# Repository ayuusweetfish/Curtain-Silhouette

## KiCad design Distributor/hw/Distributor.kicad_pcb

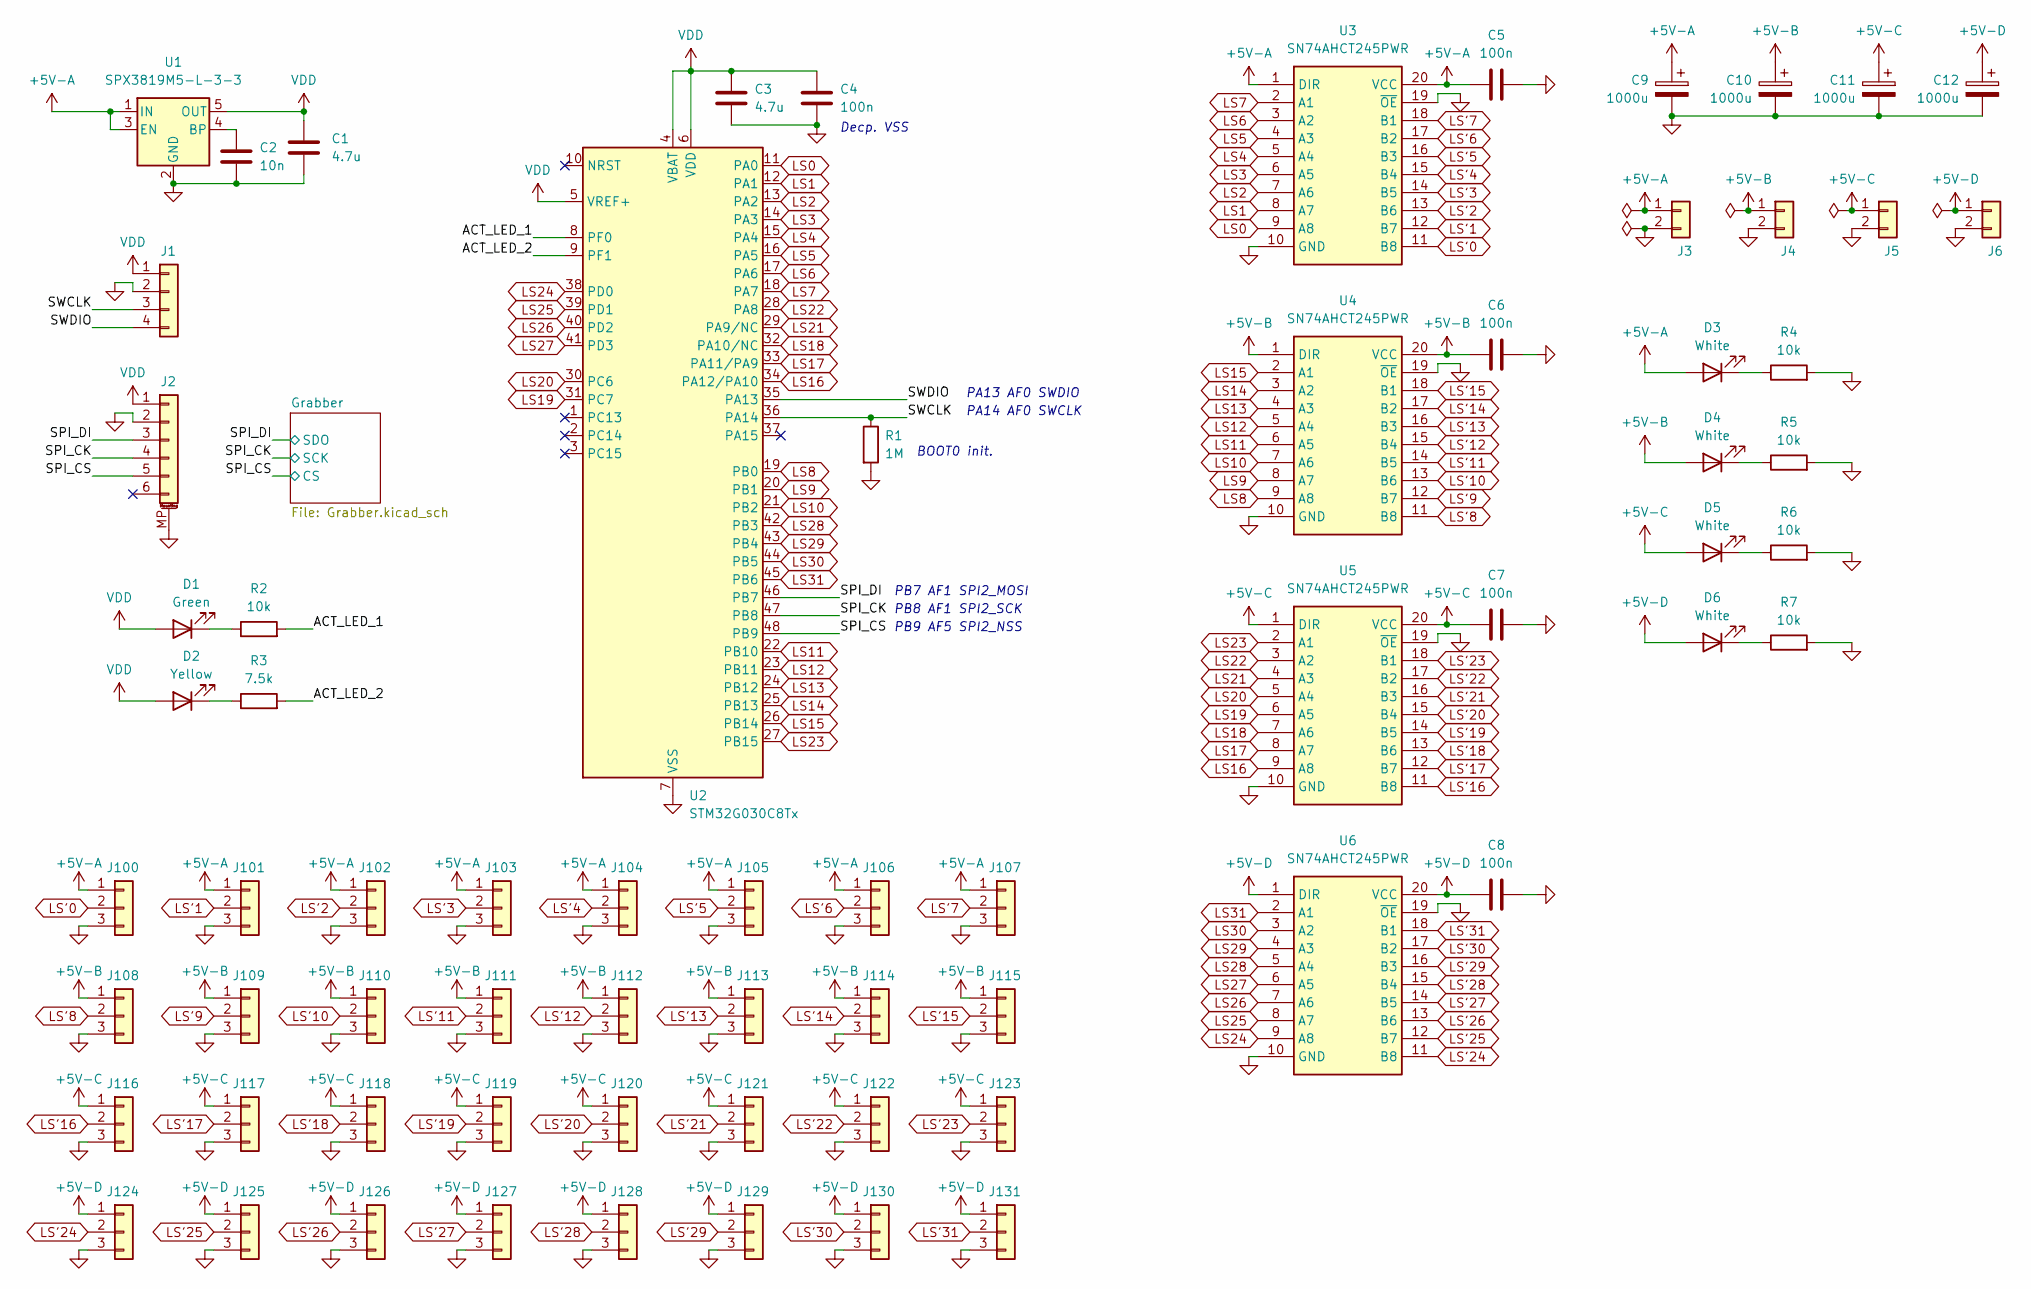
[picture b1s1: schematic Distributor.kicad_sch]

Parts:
C1, C3: 4.7u; C_0603_1608Metric
C2: 10n; C_0603_1608Metric
C4, C5, C6, C7, C8: 100n; C_0603_1608Metric
C9, C10, C11, C12: 1000u; CP_Elec_8x10.5
D1: Green; LED_0603_1608Metric
D2: Yellow; LED_0603_1608Metric
D3, D4, D5, D6: White; LED_0603_1608Metric
J1: Conn_01x04; TestPoints_1x04_P2.0
J2: Conn_01x06_MountingPin; Jushuo_AFC07-S06FCA-00_1x6-1MP_P0.50_Horizontal
J3, J4, J5, J6: Conn_01x02; PinHeader_1x02_P2.54mm_Vertical
J100, J101, J102, J103, J104, J105, J106, J107, J108, J109, J110, J111, J112, J113, J114, J115, J116, J117, J118, J119, J120, J121, J122, J123, J124, J125, J126, J127, J128, J129, J130, J131: Conn_01x03; PinHeader_1x03_P2.54mm_Vertical
R1: 1M; R_0603_1608Metric
R2, R4, R5, R6, R7: 10k; R_0603_1608Metric
R3: 7.5k; R_0603_1608Metric
U1: SPX3819M5-L-3-3; SOT-23-5
U2: STM32G030C8Tx; LQFP-48_7x7mm_P0.5mm
U3, U4, U5, U6: SN74AHCT245PWR; SOP65P640X120-20N; Manufacturer_Part_Number SN74AHCT245PWR; Mouser Part Number 595-SN74AHCT245PWR

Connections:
+5V-A: C5.1, C9.1, D3.2 (A), J3.1, J100.1, J101.1, J102.1, J103.1, J104.1, J105.1, J106.1, J107.1, U1.1 (IN), U1.3 (EN), U3.1 (DIR), U3.20 (VCC)
+5V-B: C6.1, C10.1, D4.2 (A), J4.1, J108.1, J109.1, J110.1, J111.1, J112.1, J113.1, J114.1, J115.1, U4.1 (DIR), U4.20 (VCC)
+5V-C: C7.1, C11.1, D5.2 (A), J5.1, J116.1, J117.1, J118.1, J119.1, J120.1, J121.1, J122.1, J123.1, U5.1 (DIR), U5.20 (VCC)
+5V-D: C8.1, C12.1, D6.2 (A), J6.1, J124.1, J125.1, J126.1, J127.1, J128.1, J129.1, J130.1, J131.1, U6.1 (DIR), U6.20 (VCC)
/ACT_LED_1: R2.2, U2.8 (PF0)
/ACT_LED_2: R3.2, U2.9 (PF1)
/SPI_CK: J2.4, U2.47 (PB8); also elsewhere on the board
/SPI_CS: J2.5, U2.48 (PB9); also elsewhere on the board
/SPI_DI: J2.3, U2.46 (PB7); also elsewhere on the board
/SWCLK: J1.3, R1.1, U2.36 (PA14)
/SWDIO: J1.4, U2.35 (PA13)
GND: C1.2, C2.2, C3.2, C4.2, C5.2, C6.2, C7.2, C8.2, C9.2, C10.2, C11.2, C12.2, J1.2, J2.2, J2.MP (MountPin), J3.2, J4.2, J5.2, J6.2, J100.3, J101.3, J102.3, J103.3, J104.3, J105.3, J106.3, J107.3, J108.3, J109.3, J110.3, J111.3, J112.3, J113.3, J114.3, J115.3, J116.3, J117.3, J118.3, J119.3, J120.3, J121.3, J122.3, J123.3, J124.3, J125.3, J126.3, J127.3, J128.3, J129.3, J130.3, J131.3, R1.2, R4.2, R5.2, R6.2, R7.2, U1.2 (GND), U2.7 (VSS), U3.10 (GND), U3.19 (~OE), U4.10 (GND), U4.19 (~OE), U5.10 (GND), U5.19 (~OE), U6.10 (GND), U6.19 (~OE); also elsewhere on the board
LS0: U2.11 (PA0), U3.9 (A8)
LS1: U2.12 (PA1), U3.8 (A7)
LS2: U2.13 (PA2), U3.7 (A6)
LS3: U2.14 (PA3), U3.6 (A5)
LS4: U2.15 (PA4), U3.5 (A4)
LS5: U2.16 (PA5), U3.4 (A3)
LS6: U2.17 (PA6), U3.3 (A2)
LS7: U2.18 (PA7), U3.2 (A1)
LS8: U2.19 (PB0), U4.9 (A8)
LS9: U2.20 (PB1), U4.8 (A7)
LS10: U2.21 (PB2), U4.7 (A6)
LS11: U2.22 (PB10), U4.6 (A5)
LS12: U2.23 (PB11), U4.5 (A4)
LS13: U2.24 (PB12), U4.4 (A3)
LS14: U2.25 (PB13), U4.3 (A2)
LS15: U2.26 (PB14), U4.2 (A1)
LS16: U2.34 (PA12/PA10), U5.9 (A8)
LS17: U2.33 (PA11/PA9), U5.8 (A7)
LS18: U2.32 (PA10/NC), U5.7 (A6)
LS19: U2.31 (PC7), U5.6 (A5)
LS20: U2.30 (PC6), U5.5 (A4)
LS21: U2.29 (PA9/NC), U5.4 (A3)
LS22: U2.28 (PA8), U5.3 (A2)
LS23: U2.27 (PB15), U5.2 (A1)
LS24: U2.38 (PD0), U6.9 (A8)
LS25: U2.39 (PD1), U6.8 (A7)
LS26: U2.40 (PD2), U6.7 (A6)
LS27: U2.41 (PD3), U6.6 (A5)
LS28: U2.42 (PB3), U6.5 (A4)
LS29: U2.43 (PB4), U6.4 (A3)
LS30: U2.44 (PB5), U6.3 (A2)
LS31: U2.45 (PB6), U6.2 (A1)
LS'0: J100.2, U3.11 (B8)
LS'1: J101.2, U3.12 (B7)
LS'2: J102.2, U3.13 (B6)
LS'3: J103.2, U3.14 (B5)
LS'4: J104.2, U3.15 (B4)
LS'5: J105.2, U3.16 (B3)
LS'6: J106.2, U3.17 (B2)
LS'7: J107.2, U3.18 (B1)
LS'8: J108.2, U4.11 (B8)
LS'9: J109.2, U4.12 (B7)
LS'10: J110.2, U4.13 (B6)
LS'11: J111.2, U4.14 (B5)
LS'12: J112.2, U4.15 (B4)
LS'13: J113.2, U4.16 (B3)
LS'14: J114.2, U4.17 (B2)
LS'15: J115.2, U4.18 (B1)
LS'16: J116.2, U5.11 (B8)
LS'17: J117.2, U5.12 (B7)
LS'18: J118.2, U5.13 (B6)
LS'19: J119.2, U5.14 (B5)
LS'20: J120.2, U5.15 (B4)
LS'21: J121.2, U5.16 (B3)
LS'22: J122.2, U5.17 (B2)
LS'23: J123.2, U5.18 (B1)
LS'24: J124.2, U6.11 (B8)
LS'25: J125.2, U6.12 (B7)
LS'26: J126.2, U6.13 (B6)
LS'27: J127.2, U6.14 (B5)
LS'28: J128.2, U6.15 (B4)
LS'29: J129.2, U6.16 (B3)
LS'30: J130.2, U6.17 (B2)
LS'31: J131.2, U6.18 (B1)
unnamed: D1.1 (K), R2.1
unnamed: D2.1 (K), R3.1
unnamed: D3.1 (K), R4.1
unnamed: D4.1 (K), R5.1
unnamed: D5.1 (K), R6.1
unnamed: D6.1 (K), R7.1
unnamed: C2.1, U1.4 (BP)
VDD: C1.1, C3.1, C4.1, D1.2 (A), D2.2 (A), J1.1, J2.1, U1.5 (OUT), U2.4 (VBAT), U2.5 (VREF+), U2.6 (VDD); also elsewhere on the board

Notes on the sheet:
PA14 AF0 SWCLK
PB8 AF1 SPI2_SCK
PB7 AF1 SPI2_MOSI
BOOT0 init.
Decp. VSS
PB9 AF5 SPI2_NSS
PA13 AF0 SWDIO

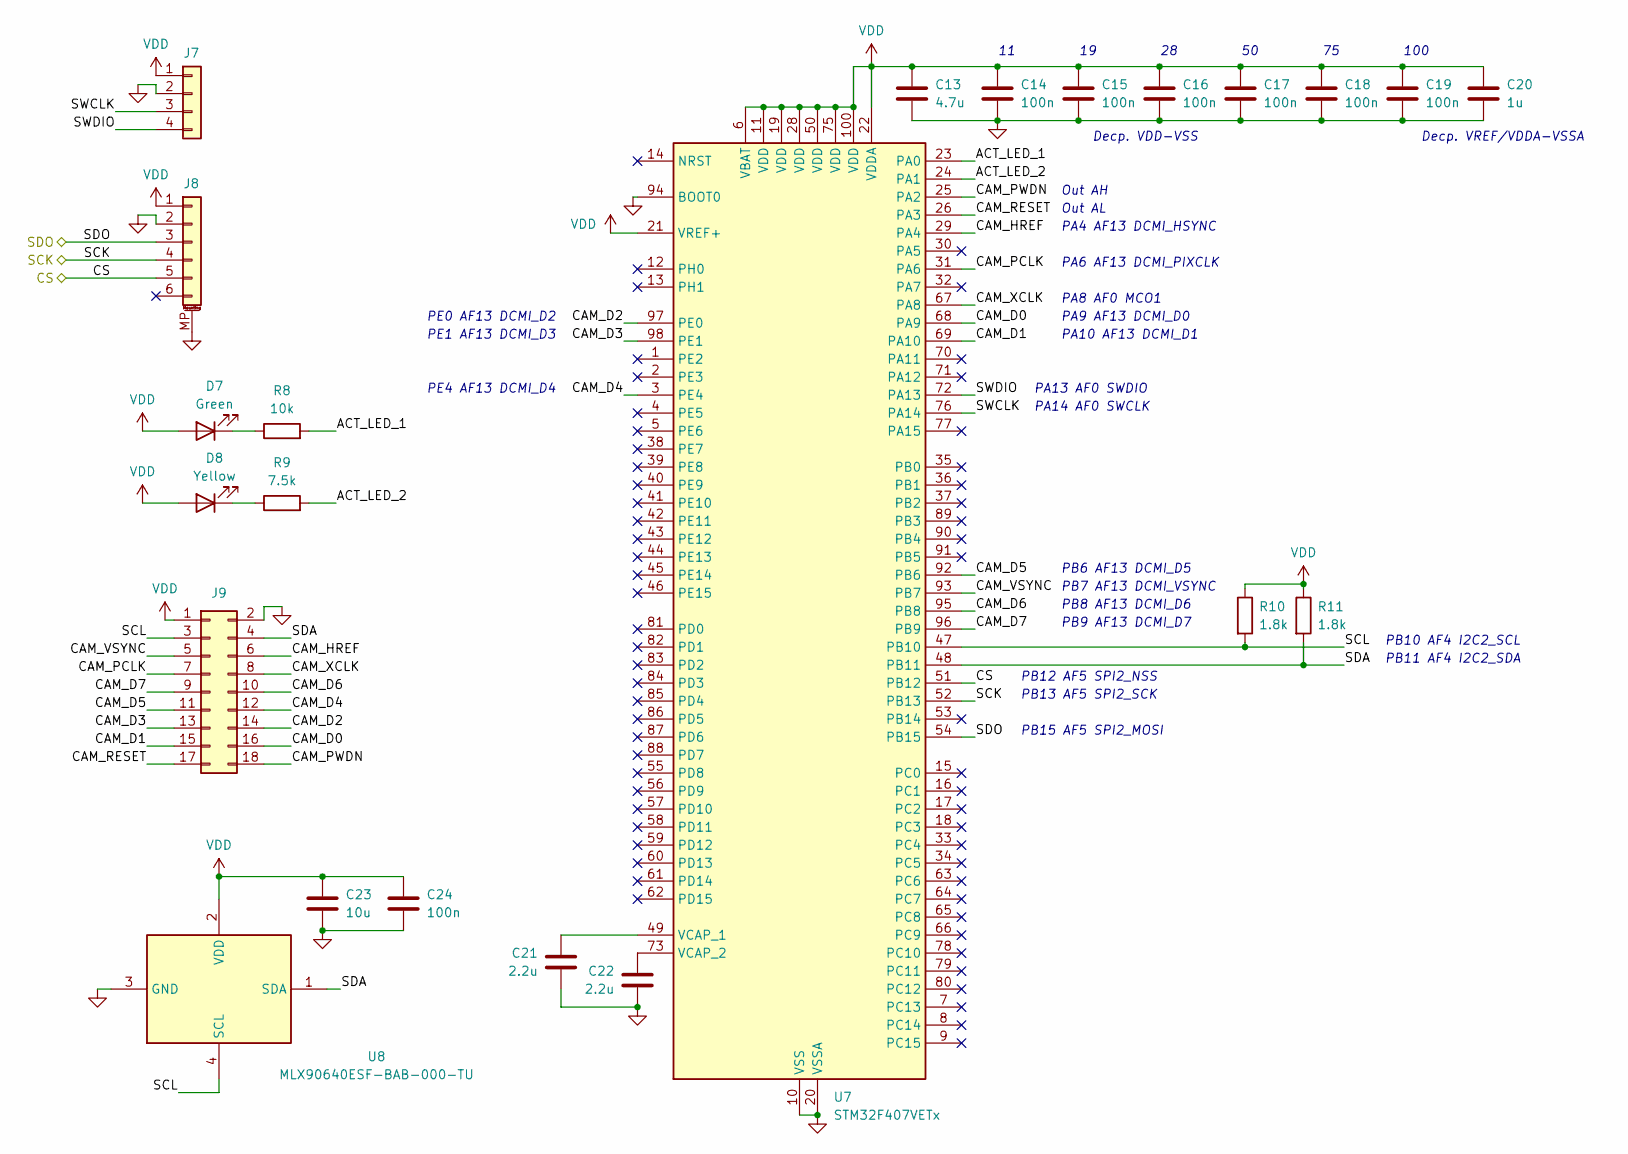
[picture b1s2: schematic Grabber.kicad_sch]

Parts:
C13: 4.7u; C_0603_1608Metric
C14, C15, C16, C17, C18, C19, C24: 100n; C_0603_1608Metric
C20: 1u; C_0603_1608Metric
C21, C22: 2.2u; C_0603_1608Metric
C23: 10u; C_0603_1608Metric
D7: Green; LED_0603_1608Metric
D8: Yellow; LED_0603_1608Metric
J7: Conn_01x04; TestPoints_1x04_P2.0
J8: Conn_01x06_MountingPin; Jushuo_AFC07-S06FCA-00_1x6-1MP_P0.50_Horizontal
J9: Conn_02x09_Odd_Even; PinHeader_2x09_P2.54mm_Vertical
R8: 10k; R_0603_1608Metric
R9: 7.5k; R_0603_1608Metric
R10, R11: 1.8k; R_0603_1608Metric
U7: STM32F407VETx; LQFP-100_14x14mm_P0.5mm
U8: MLX90640ESF-BAB-000-TU; MLX90640ESFBAB000TU; Manufacturer_Part_Number MLX90640ESF-BAB-000-TU; Mouser Part Number 482-MLX90640ESFBABTU

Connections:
/Grabber/ACT_LED_1: R8.2, U7.23 (PA0)
/Grabber/ACT_LED_2: R9.2, U7.24 (PA1)
/Grabber/CAM_D0: J9.16, U7.68 (PA9)
/Grabber/CAM_D1: J9.15, U7.69 (PA10)
/Grabber/CAM_D2: J9.14, U7.97 (PE0)
/Grabber/CAM_D3: J9.13, U7.98 (PE1)
/Grabber/CAM_D4: J9.12, U7.3 (PE4)
/Grabber/CAM_D5: J9.11, U7.92 (PB6)
/Grabber/CAM_D6: J9.10, U7.95 (PB8)
/Grabber/CAM_D7: J9.9, U7.96 (PB9)
/Grabber/CAM_HREF: J9.6, U7.29 (PA4)
/Grabber/CAM_PCLK: J9.7, U7.31 (PA6)
/Grabber/CAM_PWDN: J9.18, U7.25 (PA2)
/Grabber/CAM_RESET: J9.17, U7.26 (PA3)
/Grabber/CAM_VSYNC: J9.5, U7.93 (PB7)
/Grabber/CAM_XCLK: J9.8, U7.67 (PA8)
/Grabber/SCL: J9.3, R10.2, U7.47 (PB10), U8.4 (SCL)
/Grabber/SDA: J9.4, R11.2, U7.48 (PB11), U8.1 (SDA)
/Grabber/SWCLK: J7.3, U7.76 (PA14)
/Grabber/SWDIO: J7.4, U7.72 (PA13)
/SPI_CK: J8.4, U7.52 (PB13); also elsewhere on the board
/SPI_CS: J8.5, U7.51 (PB12); also elsewhere on the board
/SPI_DI: J8.3, U7.54 (PB15); also elsewhere on the board
GND: C13.2, C14.2, C15.2, C16.2, C17.2, C18.2, C19.2, C20.2, C21.2, C22.2, C23.2, C24.2, J7.2, J8.2, J8.MP (MountPin), J9.2, U7.10 (VSS), U7.20 (VSSA), U7.27 (VSS), U7.74 (VSS), U7.94 (BOOT0), U7.99 (VSS), U8.3 (GND); also elsewhere on the board
unnamed: D7.1 (K), R8.1
unnamed: D8.1 (K), R9.1
unnamed: C21.1, U7.49 (VCAP_1)
unnamed: C22.1, U7.73 (VCAP_2)
VDD: C13.1, C14.1, C15.1, C16.1, C17.1, C18.1, C19.1, C20.1, C23.1, C24.1, D7.2 (A), D8.2 (A), J7.1, J8.1, J9.1, R10.1, R11.1, U7.6 (VBAT), U7.11 (VDD), U7.19 (VDD), U7.21 (VREF+), U7.22 (VDDA), U7.28 (VDD), U7.50 (VDD), U7.75 (VDD), U7.100 (VDD), U8.2 (VDD); also elsewhere on the board

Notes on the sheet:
PB8 AF13 DCMI_D6
PE4 AF13 DCMI_D4
PA9 AF13 DCMI_D0
PA6 AF13 DCMI_PIXCLK
PB11 AF4 I2C2_SDA
PB9 AF13 DCMI_D7
PA8 AF0 MCO1
PE0 AF13 DCMI_D2
PB13 AF5 SPI2_SCK
Out AL
PB10 AF4 I2C2_SCL
PE1 AF13 DCMI_D3
PB12 AF5 SPI2_NSS
Decp. VREF/VDDA-VSSA
Out AH
PA10 AF13 DCMI_D1
PA4 AF13 DCMI_HSYNC
PB15 AF5 SPI2_MOSI
100
PA14 AF0 SWCLK
Decp. VDD-VSS
PB7 AF13 DCMI_VSYNC
PB6 AF13 DCMI_D5
PA13 AF0 SWDIO

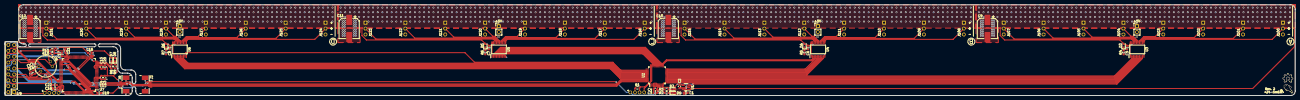
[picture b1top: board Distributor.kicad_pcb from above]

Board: 2 copper layers, 556.0 x 39.1 mm, 92 parts (0 on the bottom side), 108 nets.

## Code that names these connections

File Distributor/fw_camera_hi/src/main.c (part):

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  __HAL_RCC_GPIOE_CLK_ENABLE();
  GPIO_InitTypeDef gpio_init;

  // SWD (PA13, PA14)
  gpio_init.Pin = GPIO_PIN_13 | GPIO_PIN_14;
  gpio_init.Mode = GPIO_MODE_AF_PP; // Pass over control to AF peripheral
  gpio_init.Alternate = GPIO_AF0_SWJ;
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
  HAL_NVIC_SetPriority(SysTick_IRQn, 1, 0);

  // ======== SPI2 (PB12 CS, PB13 SCK, PB15 MOSI) ========
  gpio_init.Pin = GPIO_PIN_13 | GPIO_PIN_15;
  gpio_init.Mode = GPIO_MODE_AF_PP;
  gpio_init.Alternate = GPIO_AF5_SPI2;
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  HAL_GPIO_WritePin(GPIOA, GPIO_PIN_0, 1); HAL_Delay(80);

  // ======== Camera controls ========
  // PA2 CAM_PWDN (active high), PA3 CAM_RESET (active low)
  gpio_init = (GPIO_InitTypeDef){
    .Pin = GPIO_PIN_2 | GPIO_PIN_3,
    .Mode = GPIO_MODE_OUTPUT_PP,
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  HAL_GPIO_WritePin(GPIOA, GPIO_PIN_2, 0);
  HAL_GPIO_WritePin(GPIOA, GPIO_PIN_3, 0);  // Reset

  // ======== MCO (PB8 MCO1) ========
  // GPIO initialisation is done by `HAL_RCC_MCOConfig`
  // 168 MHz / 4 = 42 MHz
  HAL_RCC_MCOConfig(RCC_MCO1, RCC_MCO1SOURCE_PLLCLK, RCC_MCODIV_4);
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  HAL_GPIO_WritePin(GPIOA, GPIO_PIN_3, 1);  // Release reset
  HAL_Delay(2); // OV7670 datasheet t_S:RESET

  // ======== I2C2 (PB10 SCL, PB11 SDA) ========
  gpio_init = (GPIO_InitTypeDef){
    .Pin = GPIO_PIN_10 | GPIO_PIN_11,
    .Mode = GPIO_MODE_AF_OD,
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
// Test frequencies
if (0) {
  // PA4 HSYNC, PA6 PIXCLK, PA9 D0, PA10 D1
  gpio_init = (GPIO_InitTypeDef){
    .Pin = GPIO_PIN_4 | GPIO_PIN_6 | GPIO_PIN_9 | GPIO_PIN_10,
    .Mode = GPIO_MODE_INPUT,
    .Speed = GPIO_SPEED_FREQ_VERY_HIGH,
  };
  HAL_GPIO_Init(GPIOA, &gpio_init);
  // PB6 D5, PB7 VSYNC, PB8 D6, PB9 D7
  gpio_init = (GPIO_InitTypeDef){
    .Pin = GPIO_PIN_6 | GPIO_PIN_7 | GPIO_PIN_8 | GPIO_PIN_9,
    .Mode = GPIO_MODE_INPUT,
    .Speed = GPIO_SPEED_FREQ_VERY_HIGH,
  };
  HAL_GPIO_Init(GPIOB, &gpio_init);
  // PE0 D2, PE1 D3, PE4 D4
  gpio_init = (GPIO_InitTypeDef){
    .Pin = GPIO_PIN_0 | GPIO_PIN_1 | GPIO_PIN_4,
    .Mode = GPIO_MODE_INPUT,
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  HAL_NVIC_EnableIRQ(DMA2_Stream1_IRQn);

  // ======== DCMI GPIOs ========
  // PA4 HSYNC, PA6 PIXCLK, PA9 D0, PA10 D1
  gpio_init = (GPIO_InitTypeDef){
    .Pin = GPIO_PIN_4 | GPIO_PIN_6 | GPIO_PIN_9 | GPIO_PIN_10,
    .Mode = GPIO_MODE_AF_PP,
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    .Speed = GPIO_SPEED_FREQ_VERY_HIGH,
  };
  HAL_GPIO_Init(GPIOA, &gpio_init);
  // PB6 D5, PB7 VSYNC, PB8 D6, PB9 D7
  gpio_init = (GPIO_InitTypeDef){
    .Pin = GPIO_PIN_6 | GPIO_PIN_7 | GPIO_PIN_8 | GPIO_PIN_9,
    .Mode = GPIO_MODE_AF_PP,
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    .Speed = GPIO_SPEED_FREQ_VERY_HIGH,
  };
  HAL_GPIO_Init(GPIOB, &gpio_init);
  // PE0 D2, PE1 D3, PE4 D4
  gpio_init = (GPIO_InitTypeDef){
    .Pin = GPIO_PIN_0 | GPIO_PIN_1 | GPIO_PIN_4,
    .Mode = GPIO_MODE_AF_PP,
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
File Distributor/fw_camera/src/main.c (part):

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  __HAL_RCC_GPIOF_CLK_ENABLE();
  GPIO_InitTypeDef gpio_init;

  // SWD (PA13, PA14)
  gpio_init.Pin = GPIO_PIN_13 | GPIO_PIN_14;
  gpio_init.Mode = GPIO_MODE_AF_PP; // Pass over control to AF peripheral
  gpio_init.Alternate = GPIO_AF0_SWJ;
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
  HAL_NVIC_SetPriority(SysTick_IRQn, 1, 0);

  // ======== SPI2 (PB9 CS, PB8 SCK, PB7 MOSI) ========
  gpio_init.Pin = GPIO_PIN_7 | GPIO_PIN_8;
  gpio_init.Mode = GPIO_MODE_AF_PP;
  gpio_init.Alternate = GPIO_AF1_SPI2;
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  HAL_RCC_MCOConfig(RCC_MCO1, RCC_MCO1SOURCE_SYSCLK, RCC_MCODIV_4);

  // ======== GPIO (Camera) ========
  // PA3 CAM_PWDN (active high)
  // PA4 CAM_RESET (active low)
  gpio_init = (GPIO_InitTypeDef){
    .Pin = GPIO_PIN_3 | GPIO_PIN_4,
    .Mode = GPIO_MODE_OUTPUT_PP,
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  // Reset
  HAL_GPIO_WritePin(GPIOA, GPIO_PIN_4, 0);

  // ======== EXTI (PA9 CAM_VSYNC) ========
  gpio_init.Pin = GPIO_PIN_9;
  gpio_init.Mode = GPIO_MODE_INPUT;
  gpio_init.Pull = GPIO_NOPULL;
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  HAL_NVIC_SetPriority(EXTI4_15_IRQn, 0, 0);

  // ======== GPIO (Camera) ========
  // PA2 CAM_HREF
  gpio_init = (GPIO_InitTypeDef){
    .Pin = GPIO_PIN_2,
    .Mode = GPIO_MODE_INPUT,
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  };
  HAL_GPIO_Init(GPIOA, &gpio_init);

  // PB0-2, PB10-114 CAM_D
  // PB15 CAM_PCLK
  gpio_init = (GPIO_InitTypeDef){
    .Pin = GPIO_PIN_0 | GPIO_PIN_1 | GPIO_PIN_2 | GPIO_PIN_10 |
           GPIO_PIN_11 | GPIO_PIN_12 | GPIO_PIN_13 | GPIO_PIN_14 |
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  HAL_Delay(10);
  HAL_GPIO_WritePin(GPIOA, GPIO_PIN_4, 1);  // XXX: Does this actually work??

  // ======== I2C2 (PA11 SCL, PA12 SDA) ========
  gpio_init = (GPIO_InitTypeDef){
    .Pin = GPIO_PIN_11 | GPIO_PIN_12,
    .Mode = GPIO_MODE_AF_PP,
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
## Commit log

2024-05-01 ✨ Add capacitive sensor test board (LCEDA)
2024-05-01 🚧 Add camera solution schematics
2024-05-02 Add MLX90640 sensor to schematic
2024-05-02 Separate 5V power supplies into four domains
2024-05-02 Board layout
2024-05-02 🚧 Board routing
2024-05-02 Finish routing
2024-05-03 Revise distributor board; submit for fab
2024-05-09 ✨ Start firmware
2024-05-09 Also start camera submodule firmware
2024-05-09 🧪 TIM3 interrupts
2024-05-10 🚫 STM32G0 does not support DMA'ing to GPIO
    Details in comments
2024-05-10 🚧 Try to drive LED strip
    Details in comments
2024-05-10 🚧 Partly driving light strip (are we close?)
2024-05-10 Correctly driving light strip!
2024-05-10 Breathing lights!
2024-05-11 Enable MCO
2024-05-11 Send SPI from camera unit
2024-05-11 Transmit through SPI (polling)
2024-05-11 🎉 SPI reception with DMA
2024-05-12 ⏱️📷 Synchronise with camera
2024-05-12 📷 Write SCCB registers
2024-05-12 🚧 Trying to figure out camera clocks?
2024-05-12 🚧 Correctly setting up clock subdivision
2024-05-12 📸🎉 Correctly reading test patterns from camera
2024-05-12 Optimise pixel reading
2024-05-12 Read luminance only
2024-05-12 💡 Changing lights according to camera capture
2024-05-12 ✨ Transmitting two values?!
2024-05-12 🌈 Fade colours
2024-05-13 Revise schematic, replacing camera unit MCU with STM32F407Vxxx
2024-05-13 I hate layout
2024-05-13 Is this perfectionism…? (Submit for fab)
2024-05-14 Revise board routing
2024-05-14 🚧 MLX90640 read-out
2024-05-14 Revise board per manufacturability feedback
    Commit work at noon
2024-05-14 🚧 Preparing lighting refactors
2024-05-14 🚧 Refactoring in progress
2024-05-14 ✨🌈 Colourful!
2024-05-14 ✨🌈 More strips of colourfulness!
2024-05-14 Clean ups; full strip of 120 lights
2024-05-15 ☎️ Properly sending & receiving SPI (through FFC)
2024-05-15 Calculate object temperature from MLX90640 readout
2024-05-15 Modernity 😈
2024-05-16 Compactify memory usage; running all 200*25 lights
2024-05-16 Send/receive light signals from camera sub-unit
2024-05-16 ✨ Running lights from the sub-unit
2024-05-16 Test on-chip flash read/write
2024-05-16 Initial firmware for high-frequency (STM32F407) camera sub-unit
    🚧⚠️ Not tested
2024-05-17 Fix wrong value of capacitors on VCAP pins
2024-05-17 Fill lights with test pattern on startup
2024-05-18 Fix clock configuration in high-perf camera sub-unit
2024-05-18 Transmit SPI from 'F4
2024-05-18 Running lights again
2024-05-18 Write I2C (SCCB)
2024-05-18 🚧 Trying to drive DMA/DCMI
2024-05-18 Finally >~<
2024-05-19 🚧 DCMI DMA sets TEIF?
2024-05-19 🚧 Still?
2024-05-19 🚧 Finally some progress going on
2024-05-19 📷 Finally, reading data from the camera again
2024-05-19 Clean-ups
2024-05-19 🚧 Scale?
2024-05-20 📸 More reliable image capturing
2024-05-20 Light up all 32 strips
2024-05-20 Refactor; restore to continuous refresh
2024-05-20 Update running lights sent from camera unit
2024-05-20 Clean-ups for camera unit
2024-05-20 Try putting variables in CCMRAM
2024-05-20 Update EDA document with actual values in assembly
2024-05-20 Process frame >o<
2024-05-21 🔵🔴 Extract dot matrix from design document
2024-05-21 Consume frame outside capture loop
2024-05-21 (Untested) Display the pattern! ✨🚪
2024-05-21 Minor updates; successfully running
2024-05-21 🚧 (WIP) Background frame maintenance
2024-05-21 Lights apparently cannot run on '070?
2024-05-21 (Stash WIP)
2024-05-22 Various updates…
2024-05-22 (Untested) Display animation frame sequence
2024-05-23 (WIP)
2024-05-27 Prepare to test camera algorithm on desktop
2024-05-27 Resize and display image
2024-05-27 🚧 Correctly running the algorithm
2024-05-27 Upload firmware with CMSIS-DAP (QC passed)
2024-05-27 Commit missing file (silhouette_detection.h)
2024-05-27 Fix mistakes in detection algorithm
2024-05-27 Add singleton mode for detection subroutines
2024-05-27 Mangle names in singleton mode
2024-05-27 🚧 (Untested) Integrate silhouette detection subroutines into firmware
2024-05-27 🎉 Fix camera module firmware
2024-05-27 Camera unit firmware release build
2024-05-27 Implement single-pixel mild updates
2024-05-27 Add a closing step in residual image postprocessing
2024-05-28 Optimise RMQ, 🚧 circular kernel?
2024-05-28 Commit changes at production site
